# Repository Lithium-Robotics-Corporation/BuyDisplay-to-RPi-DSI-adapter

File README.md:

# Buydisplay Adapter Board
### To be used with: https://www.buydisplay.com/7-84-inch-bar-style-ips-tft-iot-lcd-display-1280x400-mipi-for-car-monitor

#### This PCB intended to allow you to connect the above MIPI DSI 2-lane LCD to a Raspberry Pi via the common 22-pin RPi DSI connector. 
#### Note that this PCB also contains an 18V backlight boost converter for driving the display's backlight array.

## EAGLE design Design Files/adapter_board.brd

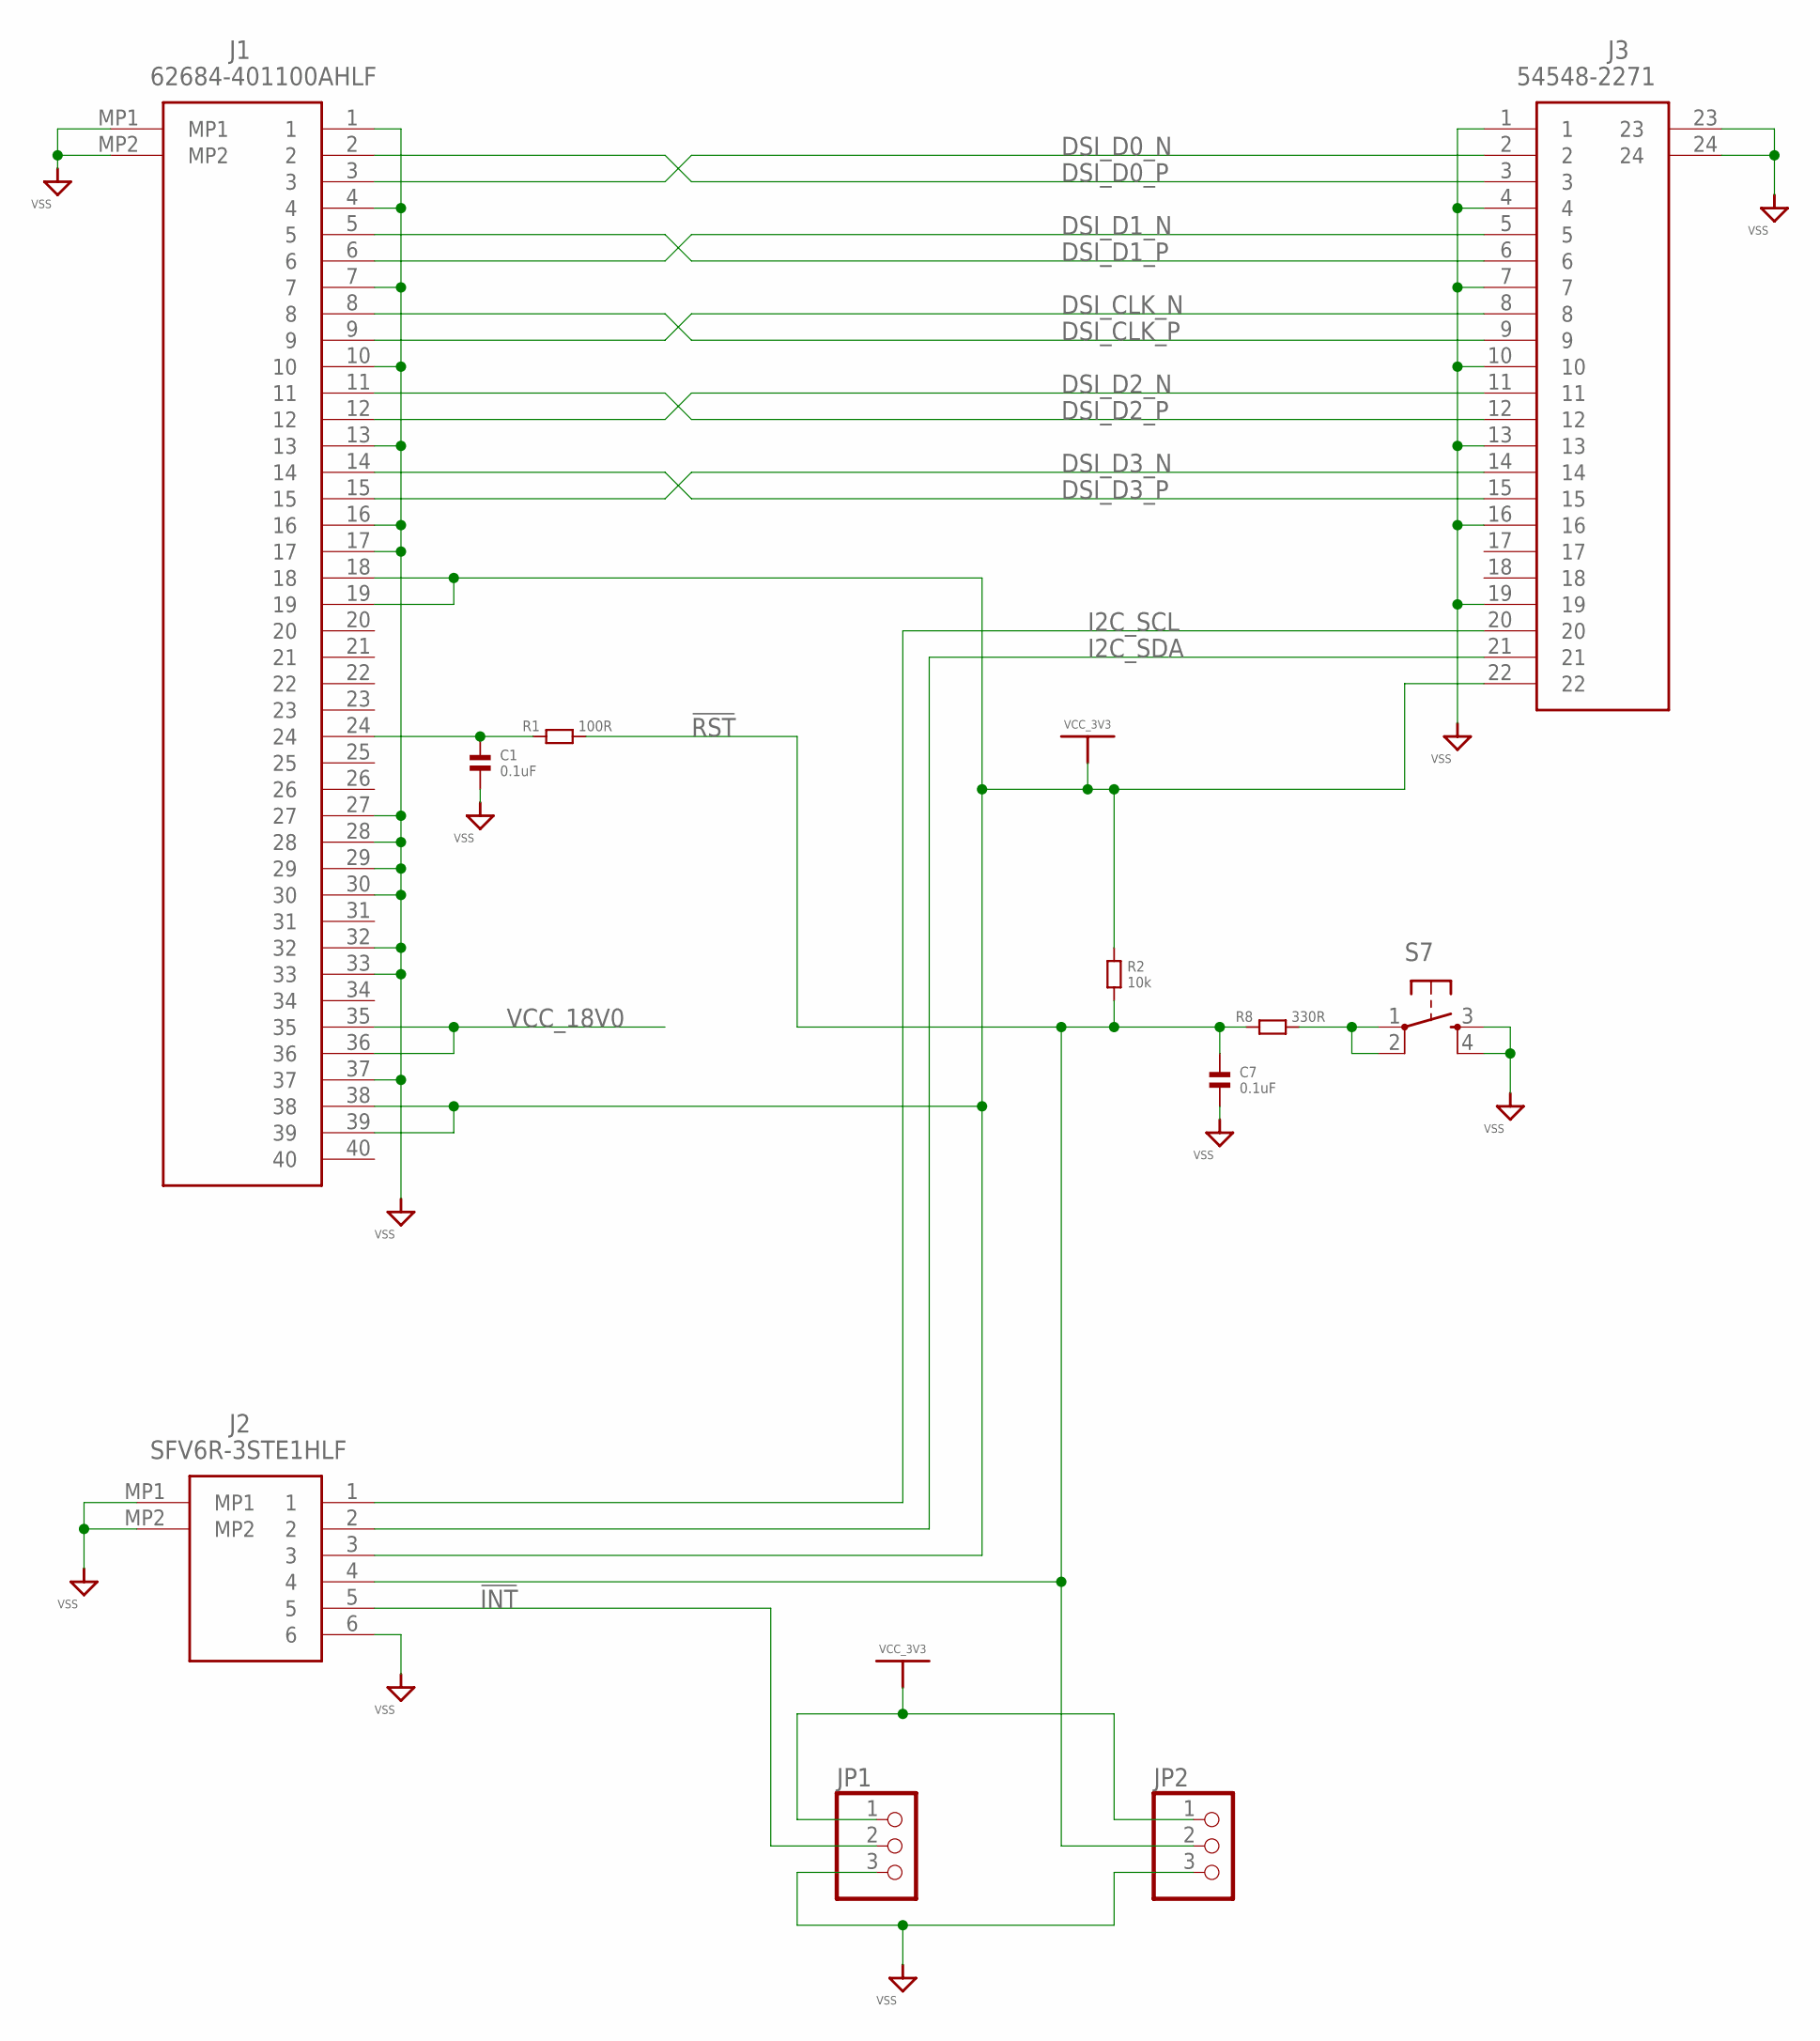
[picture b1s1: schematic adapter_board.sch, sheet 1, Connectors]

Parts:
C1, C7: 0.1uF; 0603
J1: 62684-401100AHLF; 62684401100AHLF
J2: SFV6R-3STE1HLF; SFV6R3STE1HLF
J3: 54548-2271; 545482271
JP1, JP2: PINHD-1X3; 1X03
R1: 100R; 0603
R2: 10k; 0603
R8: 330R; 0603
S7: TAC_SWITCHPTH; TACTILE-PTH

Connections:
!INT: J2.5, JP1.2
!RST: C7.1, J2.4, JP2.2, R1.2, R2.2, R8.1
DSI_CLK_N: J1.9, J3.8
DSI_CLK_P: J1.8, J3.9
DSI_D0_N: J1.3, J3.2
DSI_D0_P: J1.2, J3.3
DSI_D1_N: J1.6, J3.5
DSI_D1_P: J1.5, J3.6
DSI_D2_N: J1.12, J3.11
DSI_D2_P: J1.11, J3.12
DSI_D3_N: J1.15, J3.14
DSI_D3_P: J1.14, J3.15
I2C_SCL: J2.1, J3.20
I2C_SDA: J2.2, J3.21
unnamed: C1.1, J1.24, R1.1
unnamed: R8.2, S7.1, S7.2
VCC_3V3: J1.18, J1.19, J1.38, J1.39, J2.3, J3.22, JP1.1, JP2.1, R2.1
VCC_18V0: J1.35, J1.36; also elsewhere on the board
VSS: C1.2, C7.2, J1.1, J1.4, J1.7, J1.10, J1.13, J1.16, J1.17, J1.27, J1.28, J1.29, J1.30, J1.32, J1.33, J1.37, J1.MP1, J1.MP2, J2.6, J2.MP1, J2.MP2, J3.1, J3.4, J3.7, J3.10, J3.13, J3.16, J3.19, J3.23, J3.24, JP1.3, JP2.3, S7.3, S7.4; also elsewhere on the board

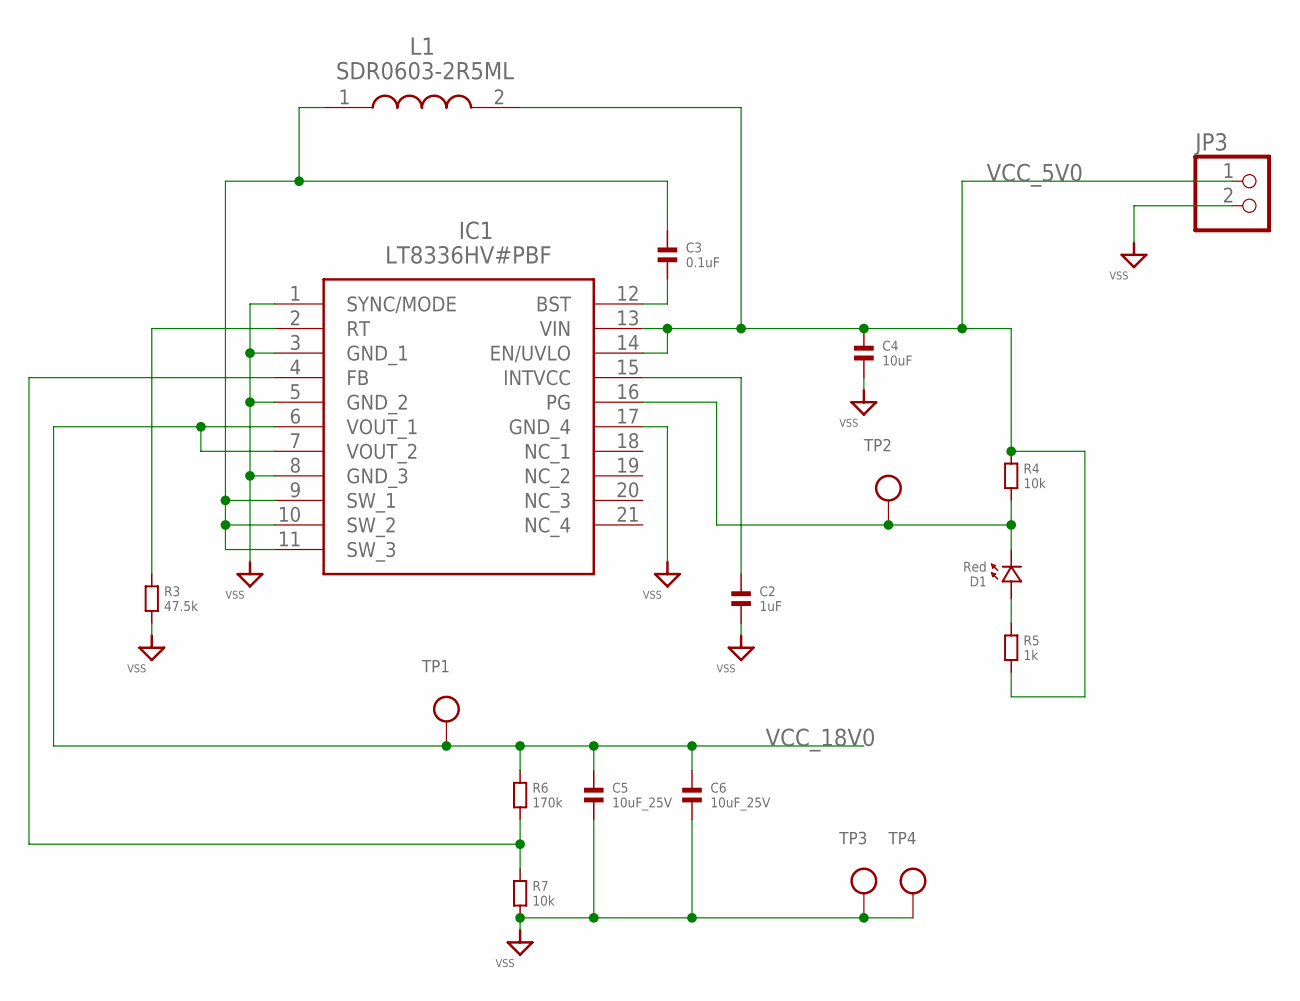
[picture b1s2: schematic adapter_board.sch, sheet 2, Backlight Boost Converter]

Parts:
C2: 1uF; 0603
C3: 0.1uF; 0603
C4: 10uF; 0603
C5, C6: 10uF_25V; 0805
D1: Red; 0603.LED
IC1: LT8336HV#PBF; LT8336HVPBF
JP3: PINHD-1X2; 1X02
L1: SDR0603-2R5ML; SDR06032R5ML
R3: 47.5k; 0603
R4, R7: 10k; 0603
R5: 1k; 0603
R6: 170k; 0603
TP1, TP2, TP3, TP4: TESTPOINTROUND1MM; TESTPOINT_ROUND_1MM

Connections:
unnamed: C2.1, IC1.15 (INTVCC)
unnamed: IC1.2 (RT), R3.1
unnamed: C3.1, IC1.9 (SW_1), IC1.10 (SW_2), IC1.11 (SW_3), L1.1
unnamed: C3.2, IC1.12 (BST)
unnamed: D1.P$2 (2), IC1.16 (PG), R4.2, TP2.P$1
unnamed: D1.P$1 (1), R5.1
unnamed: IC1.4 (FB), R6.2, R7.1
VCC_5V0: C4.1, IC1.13 (VIN), IC1.14 (EN/UVLO), JP3.1, L1.2, R4.1, R5.2
VCC_18V0: C5.1, C6.1, IC1.6 (VOUT_1), IC1.7 (VOUT_2), R6.1, TP1.P$1; also elsewhere on the board
VSS: C2.2, C4.2, C5.2, C6.2, IC1.1 (SYNC/MODE), IC1.3 (GND_1), IC1.5 (GND_2), IC1.8 (GND_3), IC1.17 (GND_4), JP3.2, R3.2, R7.2, TP3.P$1, TP4.P$1; also elsewhere on the board

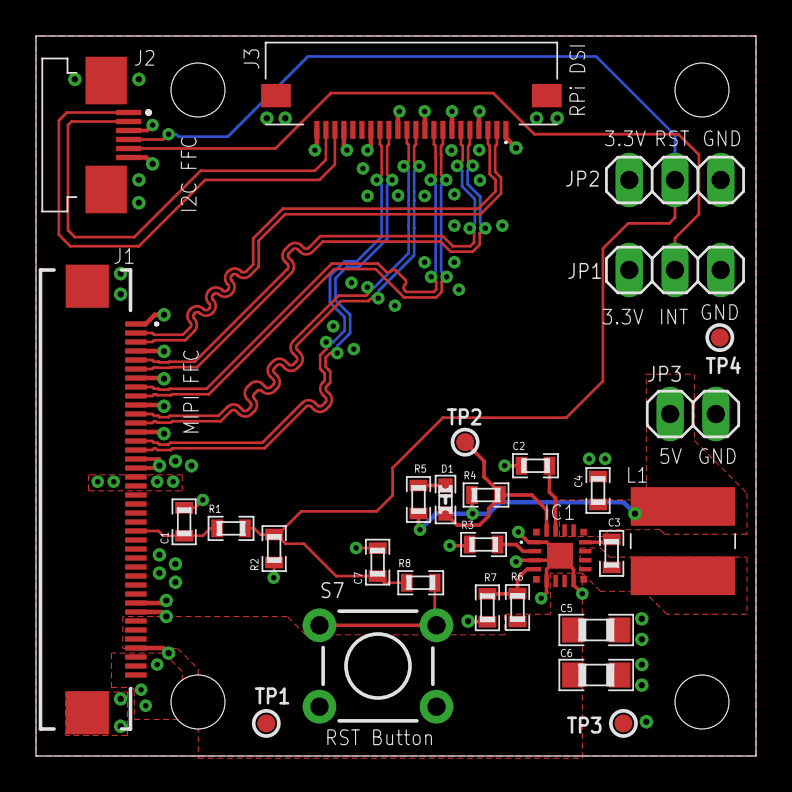
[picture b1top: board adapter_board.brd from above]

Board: 4 copper layers, 40.0 x 40.0 mm, 29 parts (0 on the bottom side), 27 nets.

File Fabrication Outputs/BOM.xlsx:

Qty | Value | Device | Package | Manufacturer | Part Number | Parts | Description
3 | 0.1uF | CAPACITOR.0603 | 0603 | KEMET | C0603C104K5RACAUTO7411 | C1, C3, C7
1 | 100R | RESISTOR.0603 | 0603 | TE Connectivity | CRGP0603F100R | R1
3 | 10k | RESISTOR.0603 | 0603 | ROHM | SDR03EZPF1002 | R2, R4, R7
1 | 10uF | CAPACITOR.0603 | 0603 | Murata | GRM188R61E106MA73J | C4
2 | 10uF_25V | CAPACITOR.0805 | 0805 | Taiyo Yuden | TMK212BBJ106MGHT | C5, C6
1 | 2.4uH | Inductor |  | Bourns | SDR0603-2R5ML | L1
1 | 170k | RESISTOR.0603 | 0603 | Bourns | CR0603-FX-1693ELF | R6
1 | 1k | RESISTOR.0603 | 0603 | ROHM | ESR03EZPJ102 | R5
1 | 1uF | CAPACITOR.0603 | 0603 | Taiyo Yuden | TMK107BJ105KA8T | C2
1 | 330R | RESISTOR.0603 | 0603 | ROHM | SFR03EZPF3300 | R8
1 | 47.5k | RESISTOR.0603 | 0603 | ROHM | SFR03EZPF4752 | R3
1 |  | 54548-2271 | 545482271 | Molex | 545482271 | J3 | FFC & FPC Connectors 0.5 FPC ZIF Hsg Assy ssy 22Ckt EmbsTp Pkg
1 |  | 62684-401100AHLF | 62684401100AHLF | Amphenol | 62684401100AHLF | J1 | FFC & FPC Connectors 62684-401100AHLF-OPUD
1 |  | LT8336HV#PBF | LT8336HVPBF | Analog Devices | LT8336HV#PBF | IC1 | Switching Voltage Regulators 40V, 2.5A Low IQ Sync Step-Up Silent Sw
1 | Red | LED.0603 | 0603.LED | Wurth | 155060SS75300 | D1
1 |  | SFV6R-3STE1HLF | SFV6R3STE1HLF | Amphenol | SFV6R-3STE1HLF | J2 | FFC & FPC Connectors 6P R/A SMT FFC/FPC 0.5mm CONT SPACING

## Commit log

2022-01-07 Almost done with schematic.
2022-01-07 Added readme
2022-01-07 Removed README.md.bak
2022-01-08 Finished backlight boost converter schematic
2022-01-08 Finished PCB. Generated fabrication data.
2022-01-08 Changed inductor L1.
2022-01-08 Changed min width/spacing to 6/6. Length matched DSI traces.
2022-02-14 Changed PGOOD LED to 5V rail.
2022-02-15 Changed D1 back to red.
2022-12-11 Cleaned up files. Updated README.

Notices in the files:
parts and their libraries:
microbuilder: This work is placed in the public domain, and may be freely used for commercial and non-commercial work with the following conditions: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
